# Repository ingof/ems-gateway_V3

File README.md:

# ems-gateway_V3

This is the eagle project of the ems-gateway board at https://emswiki.thefischer.net/

This version may be a new version. This board schould use trough-hole-monted-devices only.
The is no FDTI245RL chip for usb-serial connection.

At the moment the bootloader needs an existing FT245RL

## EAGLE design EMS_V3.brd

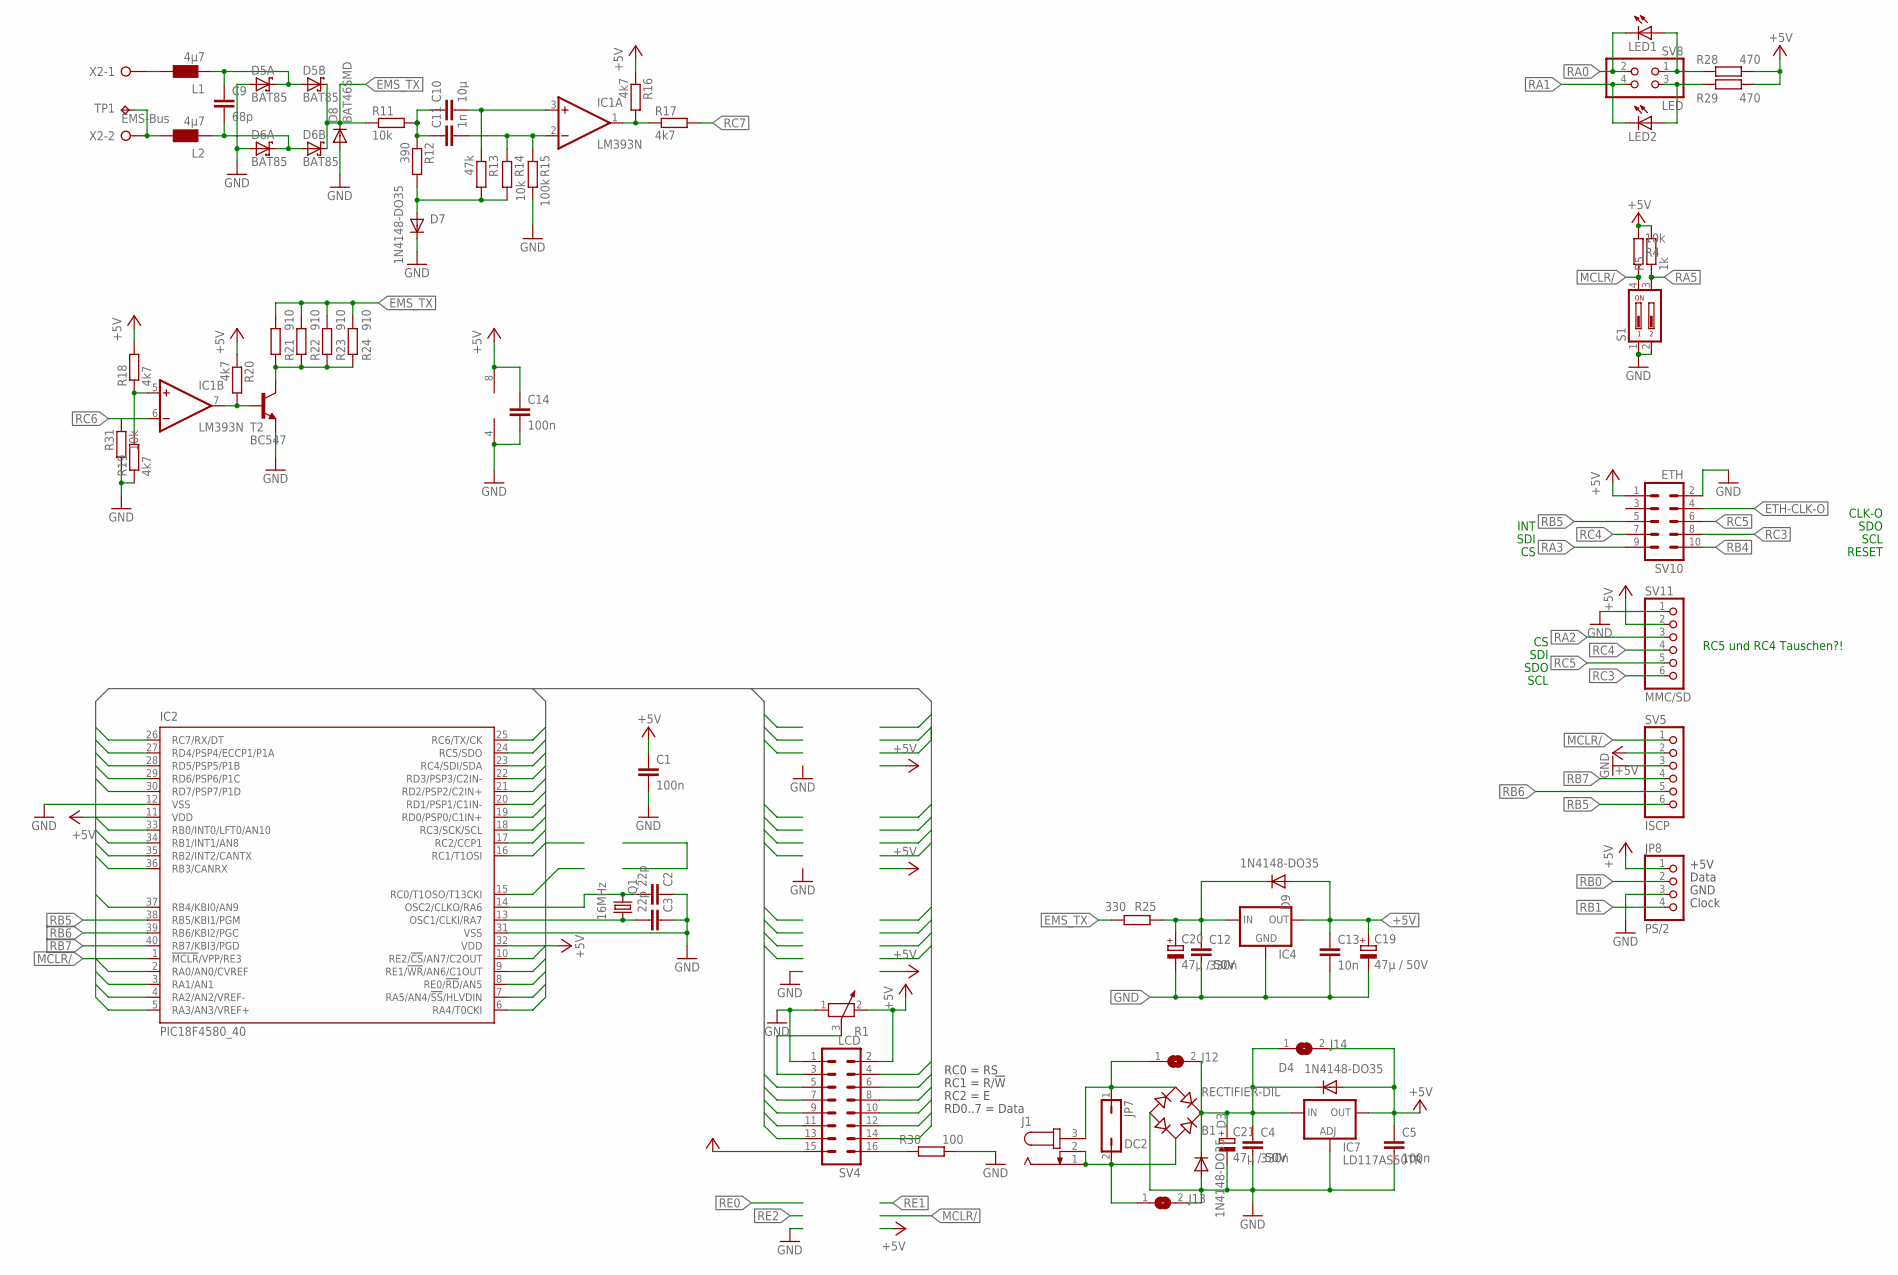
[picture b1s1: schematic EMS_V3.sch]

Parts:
B1: RECTIFIER-DIL; B-DIL
C1, C5, C14: 100n; C025-024X044
C2, C3: 22p; C025-024X044
C4, C12: 330n; C0805
C9: 68p; C0805
C10: 10µ; C050-075X075
C11: 1n; C102-043X133
C13: 10n; C0805
C19, C20, C21: 47µ / 50V; E2,5-7
D3, D4, D7, D9: 1N4148-DO35; D-2.5
D5A, D5B, D6A, D6B: BAT85; DO35-7
D8: BAT46SMD; D-2.5
IC1: LM393N; DIL08
IC2: PIC18F4580_40; DIL40
IC4: 78LXX
IC7: LD117AS50TR; SOT223
J1: JACK-PLUG0; SPC4077
J12, J13, J14: SJ
JP7: DC2; JP1
JP8: PS/2; 1X04
L1, L2: 4µ7; 1210
LED1, LED2: LED3MM
Q1: 16MHz; HC49/S
R1: POTENTIOMETER_PT-10S; PT-10S
R4, R11, R14, R31: 10k; 0207/2V
R5: 1k; 0207/2V
R12: 390; 0207/2V
R13: 47k; 0207/2V
R15: 100k; 0207/2V
R16, R17, R18, R19, R20: 4k7; 0207/2V
R21, R22, R23, R24: 910; 0207/2V
R25: 330; R0805
R28, R29: 470; 0207/2V
R30: 100; 0207/2V
S1: DP02; DP-02
SV4: LCD; MA08-2
SV5: ISCP; 1X06
SV8: LED; 2X02
SV10: ETH; MA05-2
SV11: MMC/SD; 1X06
T2: BC547; TO92
TP1: TPPAD1-13; P1-13
X2: EMS-Bus; W237-132

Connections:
+5V: C1.1, C5.1, C13.1, C14.1, C19.+, D4.A, D9.A, IC1.8 (V+), IC2.11 (VDD), IC2.32 (VDD), IC4.OUT, IC7.4 (OUT), J14.2, JP8.1, R1.2, R4.1, R5.2, R16.1, R18.2, R20.1, R28.1, R29.1, SV4.2, SV4.15, SV5.2, SV10.1, SV11.2
EMS_TX: D5B.C, D6B.C, D8.C, R11.1, R21.1, R22.1, R23.1, R24.1, R25.1
ETH-CLK-O: SV10.4
GND: B1.-, C1.2, C2.1, C3.1, C4.2, C5.2, C12.2, C13.2, C14.2, C19.-, C20.-, C21.-, D3.A, D5A.A, D6A.A, D7.C, D8.A, IC1.4 (V-), IC2.12 (VSS), IC2.31 (VSS), IC4.GND, IC7.1 (ADJ), J13.2, JP8.3, R1.1, R15.2, R19.1, R30.1, R31.2, S1.1, S1.2, SV4.1, SV5.3, SV10.2, SV11.1, T2.1 (E)
MCLR/: IC2.1 (!MCLR!/VPP/RE3), R4.2, S1.4, SV5.1
unnamed: C2.2, IC2.14 (OSC2/CLKO/RA6), Q1.2
unnamed: C3.2, IC2.13 (OSC1/CLKI/RA7), Q1.1
unnamed: R1.3, SV4.3
unnamed: B1.AC1, J1.1, J1.2, J13.1, JP7.2
unnamed: C9.1, D5A.C, D5B.A, L1.1
unnamed: L2.2, TP1.TP, X2.2
unnamed: L1.2, X2.1
unnamed: C10.1, C11.1, R11.2, R12.1
unnamed: D7.A, R12.2, R13.2, R14.2
unnamed: IC1.1 (OUT), R16.2, R17.1
unnamed: C10.2, IC1.3 (+IN), R13.1
unnamed: C11.2, IC1.2 (-IN), R14.1, R15.1
unnamed: C9.2, D6A.C, D6B.A, L2.1
unnamed: C12.1, C20.+, D9.C, IC4.IN, R25.2
unnamed: R21.2, R22.2, R23.2, R24.2, T2.3 (C)
unnamed: IC1.5 (+IN), R18.1, R19.2
unnamed: IC1.7 (OUT), R20.2, T2.2 (B)
unnamed: B1.+, C4.1, C21.+, D3.C, D4.C, IC7.3 (IN), J12.2, J14.1
unnamed: LED1.A, R28.2, SV8.1
unnamed: LED2.A, R29.2, SV8.3
unnamed: R30.2, SV4.16
unnamed: B1.AC2, J1.3, J12.1, JP7.1
RA0: IC2.2 (RA0/AN0/CVREF), LED1.K (C), SV8.2
RA1: IC2.3 (RA1/AN1), LED2.K (C), SV8.4
RA2: IC2.4 (RA2/AN2/VREF-), SV11.3
RA3: IC2.5 (RA3/AN3/VREF+), SV10.9
RA4: IC2.6 (RA4/T0CKI)
RA5: IC2.7 (RA5/AN4/!SS!/HLVDIN), R5.1, S1.3
RB0: IC2.33 (RB0/INT0/LFT0/AN10), JP8.2
RB1: IC2.34 (RB1/INT1/AN8), JP8.4
RB2: IC2.35 (RB2/INT2/CANTX)
RB3: IC2.36 (RB3/CANRX)
RB4: IC2.37 (RB4/KBI0/AN9), SV10.10
RB5: IC2.38 (RB5/KBI1/PGM), SV5.6, SV10.5
RB6: IC2.39 (RB6/KBI2/PGC), SV5.5
RB7: IC2.40 (RB7/KBI3/PGD), SV5.4
RC0: IC2.15 (RC0/T1OSO/T13CKI), SV4.4
RC1: IC2.16 (RC1/T1OSI), SV4.5
RC2: IC2.17 (RC2/CCP1), SV4.6
RC3: IC2.18 (RC3/SCK/SCL), SV10.8, SV11.6
RC4: IC2.23 (RC4/SDI/SDA), SV10.7, SV11.4
RC5: IC2.24 (RC5/SDO), SV10.6, SV11.5
RC6: IC1.6 (-IN), IC2.25 (RC6/TX/CK)
RC7: IC2.26 (RC7/RX/DT), R17.2
RD0: IC2.19 (RD0/PSP0/C1IN+), SV4.7
RD1: IC2.20 (RD1/PSP1/C1IN-), SV4.8
RD2: IC2.21 (RD2/PSP2/C2IN+), SV4.9
RD3: IC2.22 (RD3/PSP3/C2IN-), SV4.10
RD4: IC2.27 (RD4/PSP4/ECCP1/P1A), SV4.11
RD5: IC2.28 (RD5/PSP5/P1B), SV4.12
RD6: IC2.29 (RD6/PSP6/P1C), SV4.13
RD7: IC2.30 (RD7/PSP7/P1D), SV4.14
RE0: IC2.8 (RE0/!RD!/AN5)
RE1: IC2.9 (RE1/!WR!/AN6/C1OUT)
RE2: IC2.10 (RE2/!CS!/AN7/C2OUT)

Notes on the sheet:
Clock
Data
+5V
GND
RC0 = RS
RC2 = E
RD0..7 = Data
RC1 = R/!W!
CLK-O
RESET
INT
RC5 und RC4 Tauschen?!
SCL
SDI
SDO

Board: 2 copper layers, 70 parts (0 on the bottom side), 53 nets, no tracks yet.

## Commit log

2016-09-11 initial file upload
